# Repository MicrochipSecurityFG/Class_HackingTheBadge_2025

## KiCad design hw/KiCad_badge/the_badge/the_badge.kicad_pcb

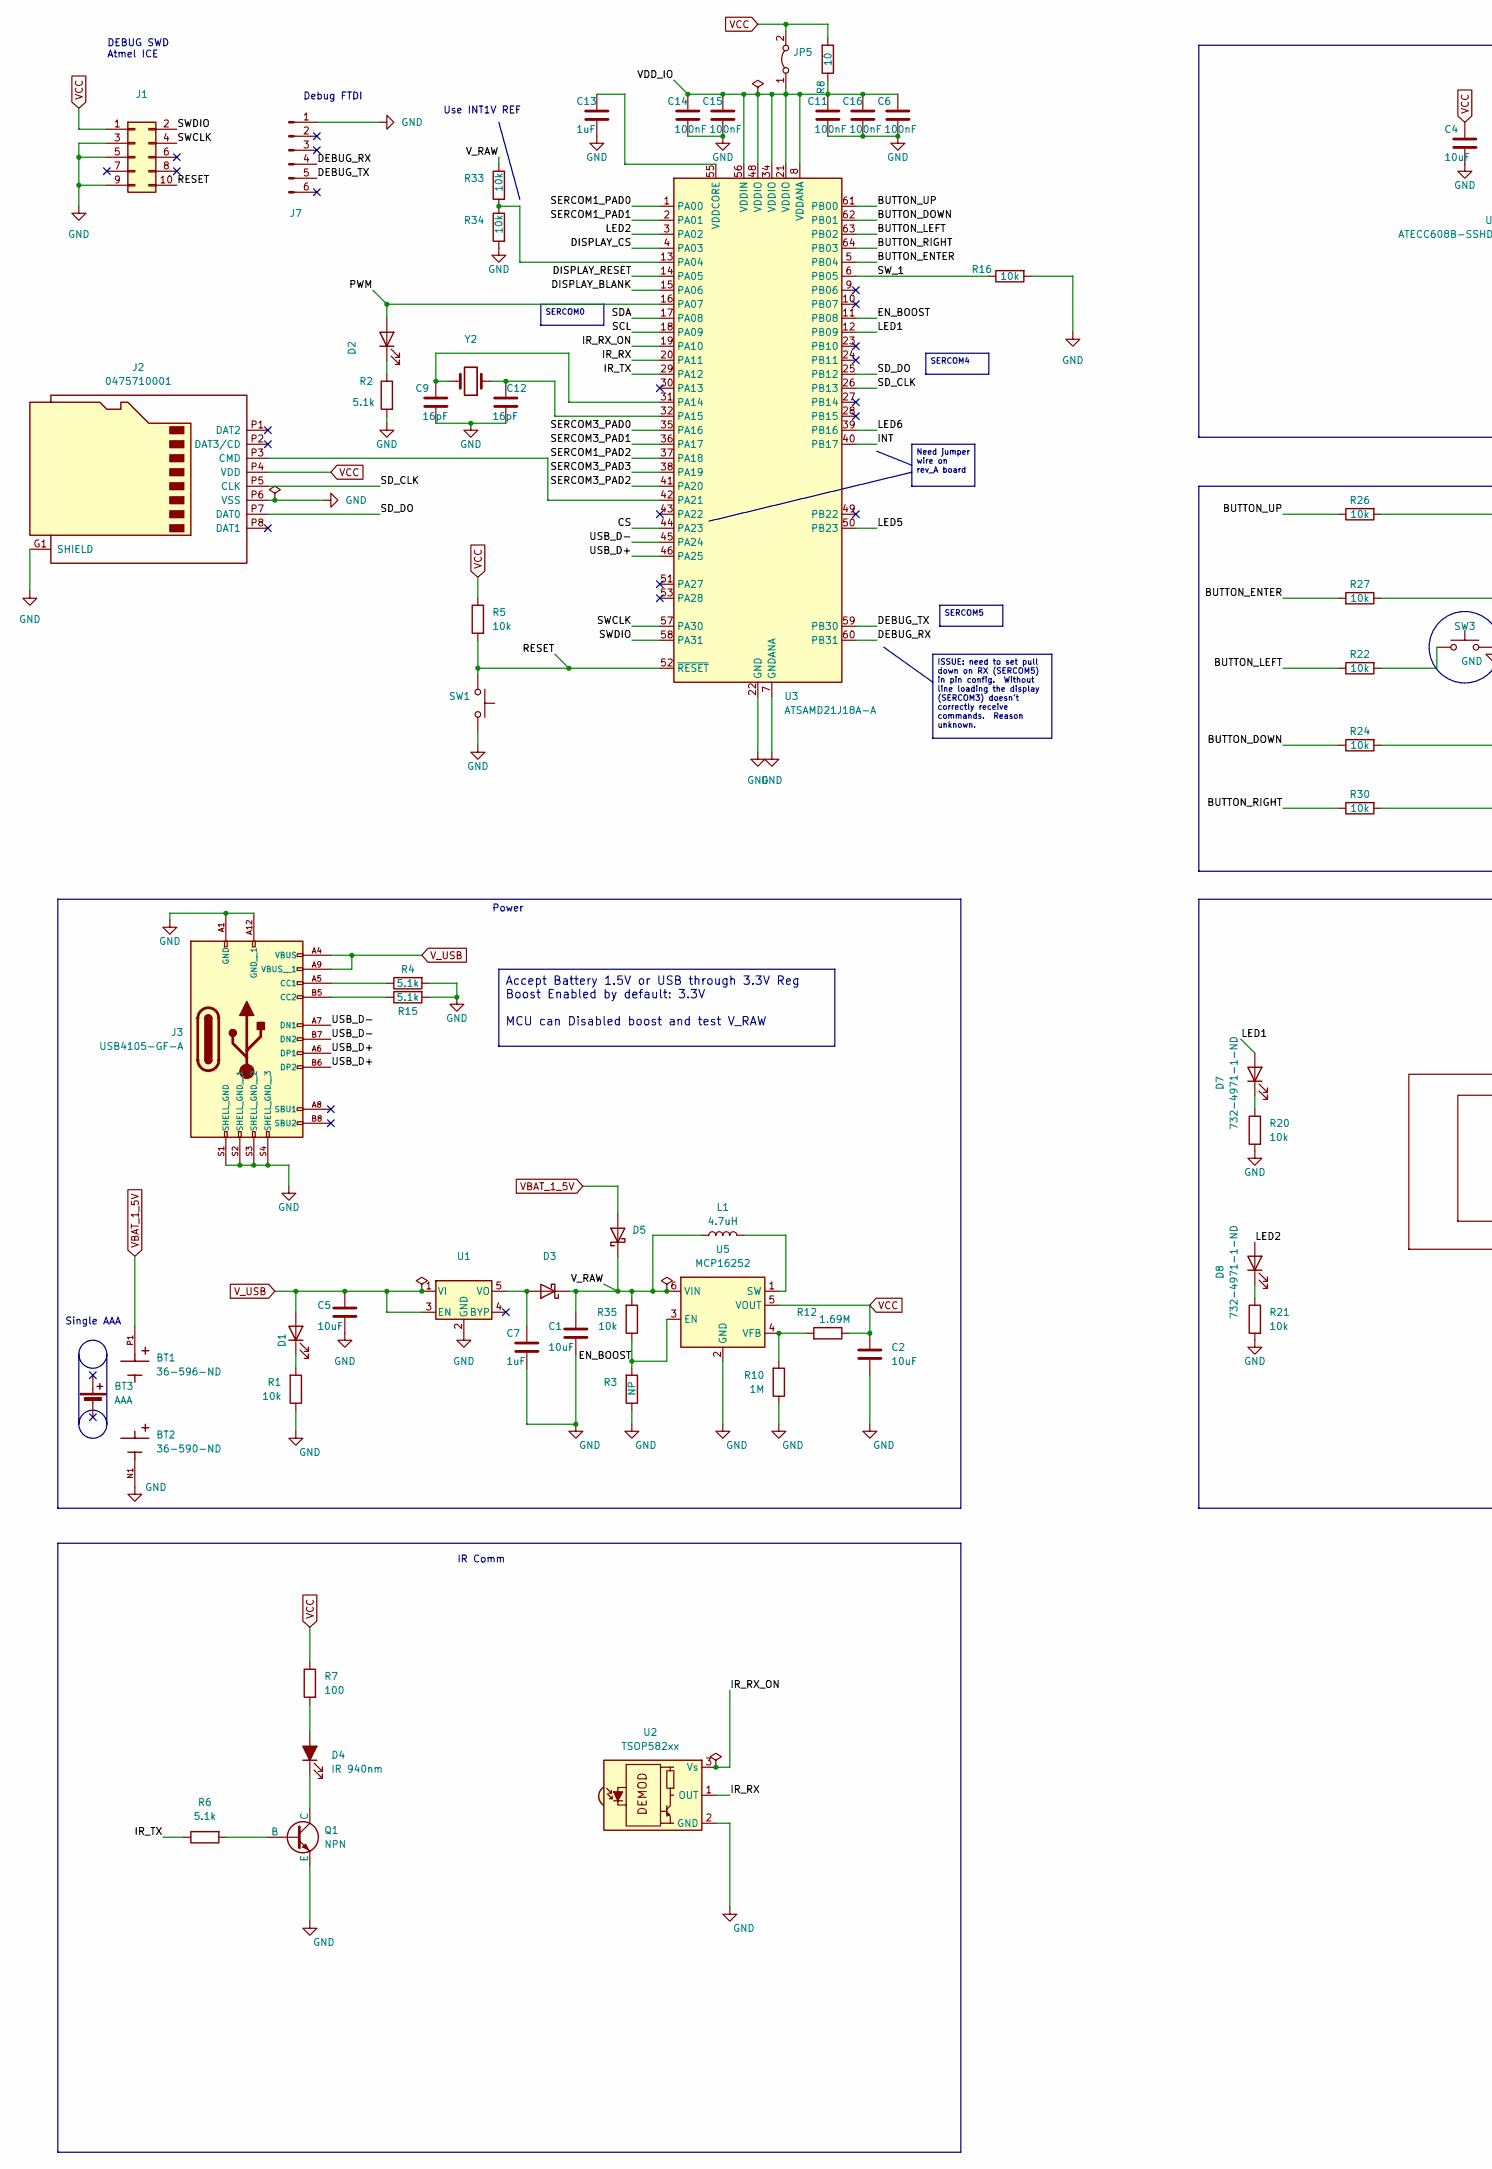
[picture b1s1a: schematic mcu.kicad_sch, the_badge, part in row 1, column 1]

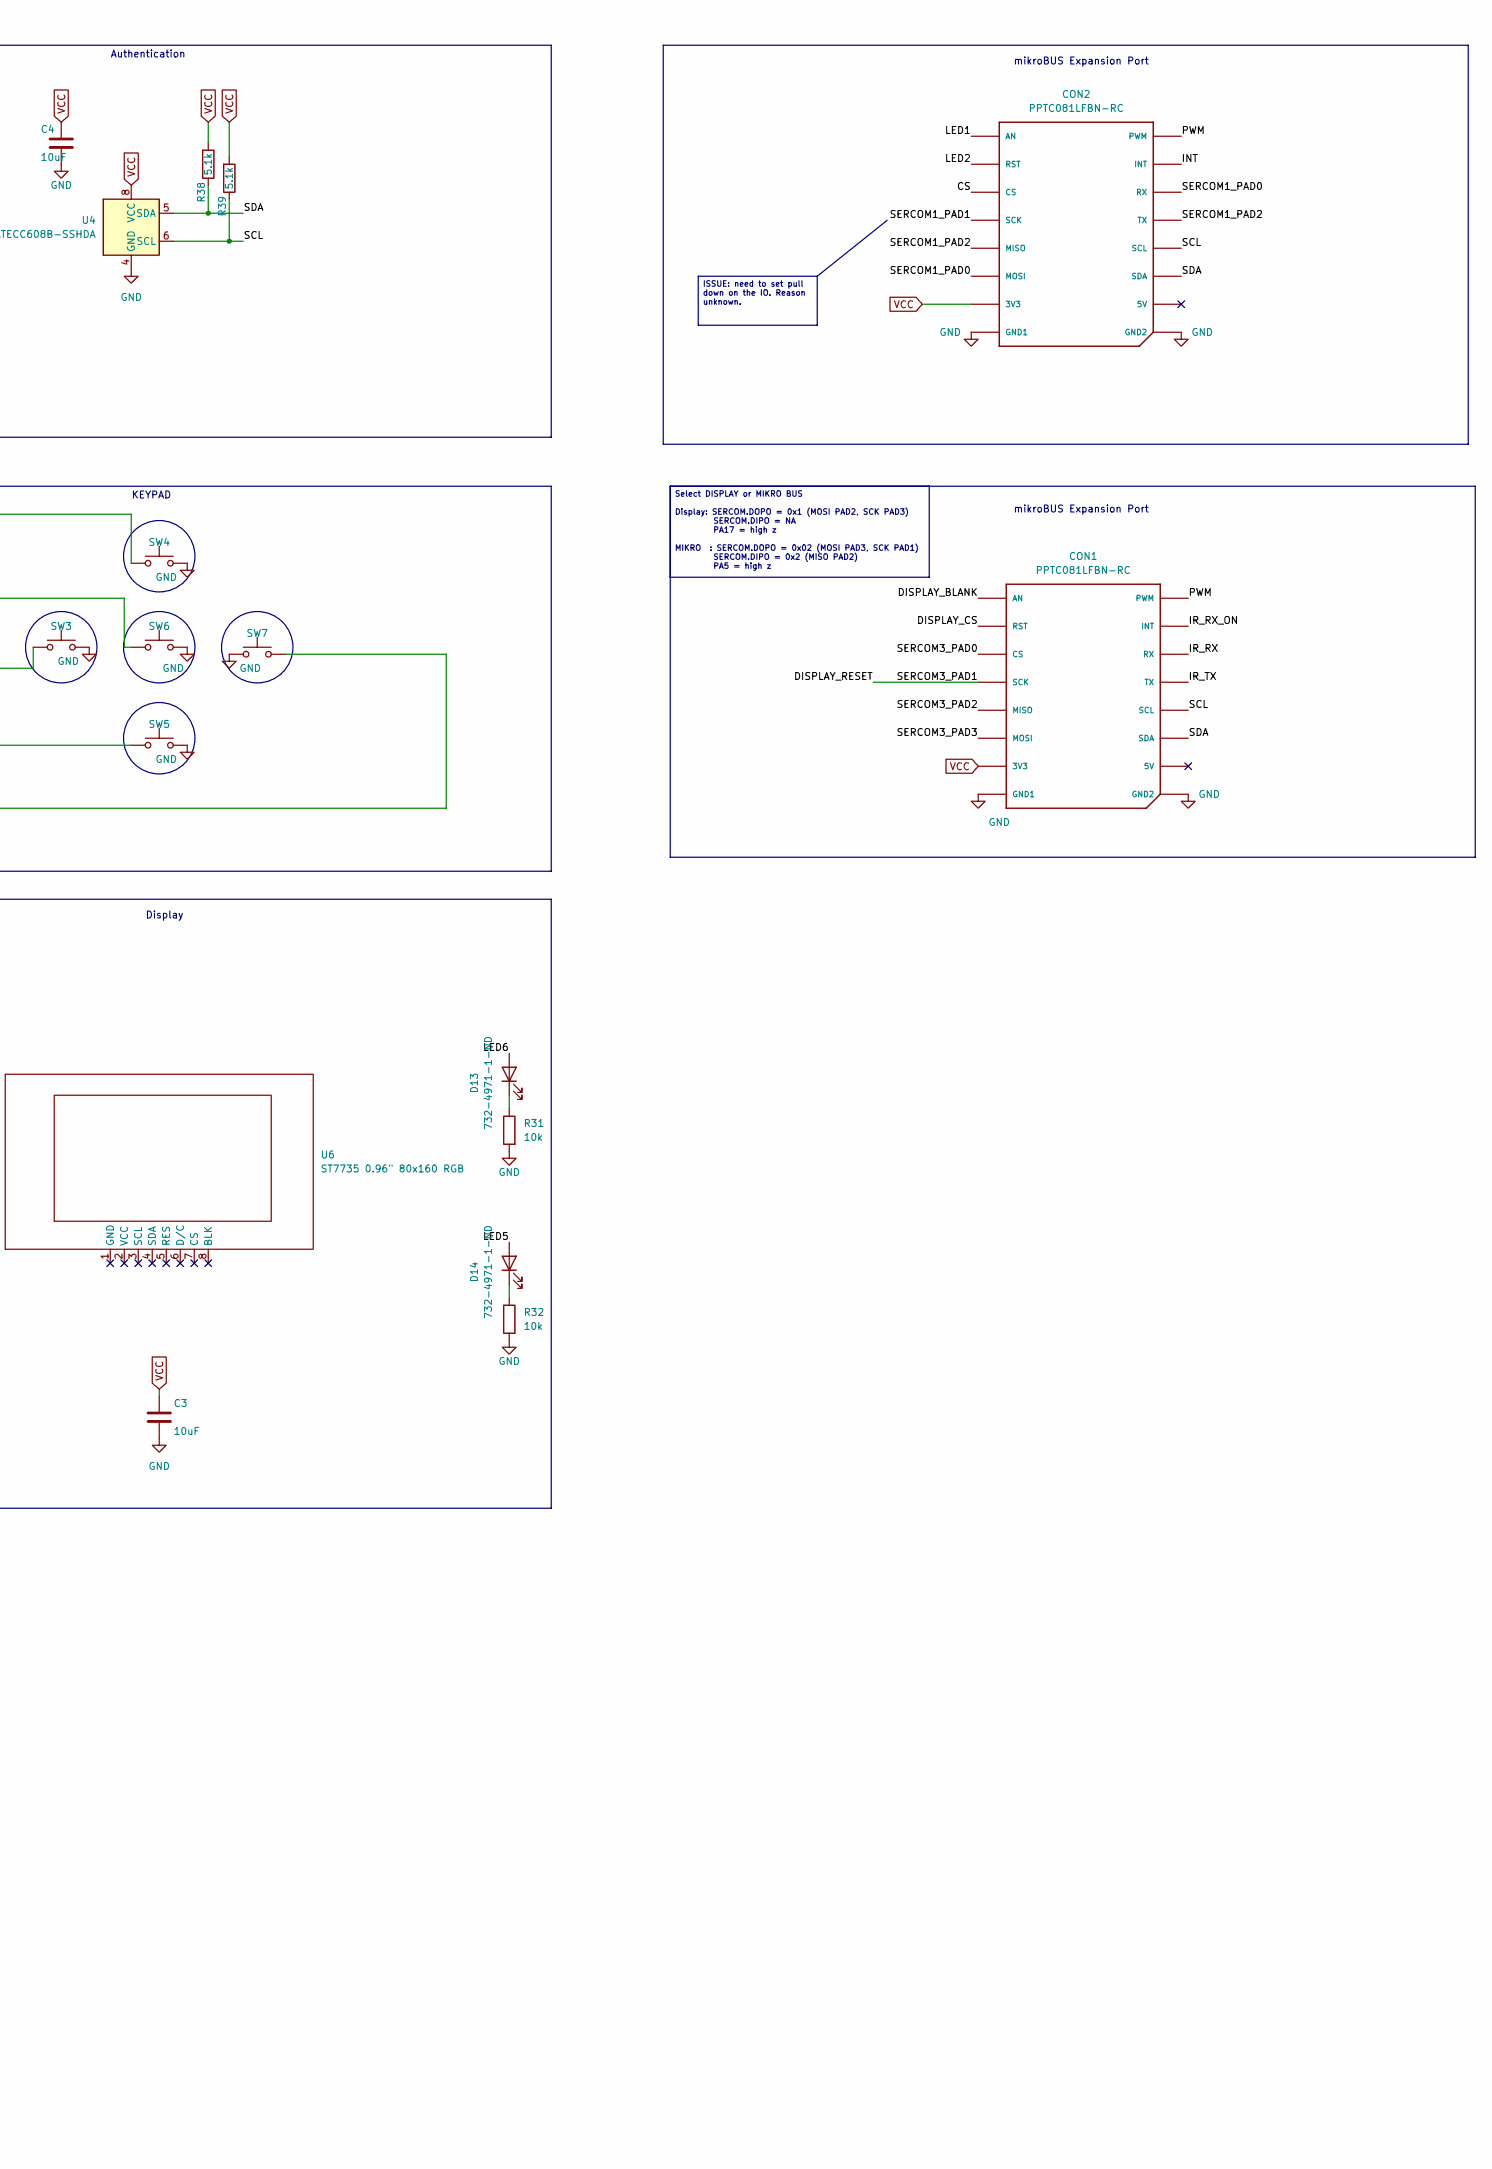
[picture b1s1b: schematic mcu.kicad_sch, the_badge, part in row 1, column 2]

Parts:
BT1: 36-596-ND; BAT_596; PARTREV D; Digikey 36-596-ND
BT2: 36-590-ND; BAT_590; PARTREV E; Digikey 36-590-ND
BT3: AAA; BatteryHolder_Keystone_2466_1xAAA
C1, C2, C3, C4, C5: 10uF; C_0603_1608Metric; Digikey 587-5869-1-ND
C6, C11, C14, C15, C16: 100nF; C_0603_1608Metric; Digikey 311-1088-1-ND
C7, C13: 1uF; C_0603_1608Metric; Digikey 311-1446-1-ND
C9, C12: 16pF; C_0603_1608Metric; Digikey 311-3964-1-ND
CON1, CON2: PPTC081LFBN-RC; MIKROBUS_HOST_CONN
D1, D2, D7, D8, D13, D14: 732-4971-1-ND; LED_0603_1608Metric; Digikey 732-4971-1-ND
D3, D5: D_Schottky; D_SOD-523; Digikey RB520S30T1GOSCT-ND
D4: IR 940nm; LED_0603_1608Metric; Digikey 3147-B13V1IR--20C000114U1930CT-ND
J1: 1156861; PinHeader_2x05_P1.27mm_Vertical_SMD; Digikey 277-1156861CT-ND
J2: 0475710001; 47571-0001_MOL; Digikey WM9731CT-ND
J3: USB4105-GF-A; USB_C_Receptacle_GCT_USB4105-xx-A_16P_TopMnt_Horizontal; PARTREV B3; Digikey 2073-USB4105-GF-ACT-ND
J7: Conn_01x06_Pin; PinHeader_1x06_P2.54mm_Vertical; Digikey 732-5319-ND
JP5: M50-3530242; PinHeader_1x02_P2.54mm_Vertical; Digikey SAM1112-02-ND (use cheaper part here), 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
L1: 4.7uH; L_0805_2012Metric; Digikey 445-8659-1-ND
Q1: NPN; SOT-23-3; Digikey MMBT3904-FDICT-ND
R1, R5, R16, R20, R21, R22, R24, R26, R27, R30, R31, R32, R33, R34, R35: 10k; R_0603_1608Metric; Digikey 311-10.0KHRCT-ND
R2, R4, R6, R15, R38, R39: 5.1k; R_0603_1608Metric; Digikey 311-5.10KHRCT-ND
R3: NP; R_0603_1608Metric; Digikey NA
R7: 100; R_0603_1608Metric; Digikey 311-100HRCT-ND
R8: 10; R_0603_1608Metric; Digikey 311-10.0HRCT-ND
R10: 1M; R_0603_1608Metric; Digikey 311-1.00MHRCT-ND
R12: 1.69M; R_0603_1608Metric; Digikey 13-RC0603FR-071M69LCT-ND
SW1, SW3, SW4, SW5, SW6, SW7: TS02-66-70-BK-160-LCR-D; SW_PUSH_6mm_H4.3mm; Digikey 2223-TS02-66-70-BK-160-LCR-D-ND
U1: MIC5301; TSOP-5_1.65x3.05mm_P0.95mm; Digikey 576-2840-1-ND
U2: TSOP582xx; Vishay_MINICAST-3Pin; Digikey TSOP58238-ND
U3: ATSAMD21J18A-A; TQFP-64_10x10mm_P0.5mm; Digikey ATSAMD21J18A-AUTCT-ND
U4: ATECC608B-SSHDA; SOIC-8_3.9x4.9mm_P1.27mm; Digikey 150-ATECC608B-SSHDA-TCT-ND
U5: MCP16252; SOT-23-6; Digikey MCP16252T-I/CHCT-ND
U6: ST7735 0.96" 80x160 RGB; Digikey NA
Y2: 049SS2-24.000F20DTLJK; Crystal_SMD_HC49-SD; Digikey XC1001CT-ND

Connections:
/mcu/BUTTON_DOWN: R24.1, U3.62 (PB01)
/mcu/BUTTON_ENTER: R27.2, U3.5 (PB04)
/mcu/BUTTON_LEFT: R22.1, U3.63 (PB02)
/mcu/BUTTON_RIGHT: R30.1, U3.64 (PB03)
/mcu/BUTTON_UP: R26.1, U3.61 (PB00)
/mcu/CS: CON2.P3 (CS), U3.44 (PA23)
/mcu/DEBUG_RX: J7.4, U3.60 (PB31)
/mcu/DEBUG_TX: J7.5, U3.59 (PB30)
/mcu/DISPLAY_BLANK: CON1.P1 (AN), U3.15 (PA06)
/mcu/DISPLAY_CS: CON1.P2 (RST), U3.4 (PA03)
/mcu/DISPLAY_RESET: CON1.P4 (SCK), U3.14 (PA05), U3.36 (PA17)
/mcu/EN_BOOST: R3.2, R35.1, U3.11 (PB08), U5.3 (EN)
/mcu/INT: CON2.P15 (INT), U3.40 (PB17)
/mcu/IR_RX: CON1.P14 (RX), U2.1 (OUT), U3.20 (PA11)
/mcu/IR_RX_ON: CON1.P15 (INT), U2.3 (Vs), U3.19 (PA10)
/mcu/IR_TX: CON1.P13 (TX), R6.1, U3.29 (PA12)
/mcu/LED1: CON2.P1 (AN), D7.2 (A), U3.12 (PB09)
/mcu/LED2: CON2.P2 (RST), D8.2 (A), U3.3 (PA02)
/mcu/LED5: D14.2 (A), U3.50 (PB23)
/mcu/LED6: D13.2 (A), U3.39 (PB16)
/mcu/PWM: CON1.P16 (PWM), CON2.P16 (PWM), D2.2 (A), U3.16 (PA07)
/mcu/RESET: J1.10, R5.2, SW1.2, U3.52 (~RESET)
/mcu/SCL: CON1.P12 (SCL), CON2.P12 (SCL), R39.1, U3.18 (PA09), U4.6 (SCL)
/mcu/SDA: CON1.P11 (SDA), CON2.P11 (SDA), R38.1, U3.17 (PA08), U4.5 (SDA)
/mcu/SD_CLK: J2.P5 (CLK), U3.26 (PB13)
/mcu/SD_DO: J2.P7 (DAT0), U3.25 (PB12)
/mcu/SERCOM1_PAD0: CON2.P6 (MOSI), CON2.P14 (RX), U3.1 (PA00)
/mcu/SERCOM1_PAD1: CON2.P4 (SCK), U3.2 (PA01)
/mcu/SERCOM1_PAD2: CON2.P5 (MISO), CON2.P13 (TX), U3.37 (PA18)
/mcu/SERCOM3_PAD0: CON1.P3 (CS), U3.35 (PA16)
/mcu/SERCOM3_PAD2: CON1.P5 (MISO), U3.41 (PA20)
/mcu/SERCOM3_PAD3: CON1.P6 (MOSI), U3.38 (PA19)
/mcu/SWCLK: J1.4, U3.57 (PA30)
/mcu/SWDIO: J1.2, U3.58 (PA31)
/mcu/SW_1: R16.1, U3.6 (PB05)
/mcu/USB_D+: J3.A6 (DP1), J3.B6 (DP2), U3.46 (PA25)
/mcu/USB_D-: J3.A7 (DN1), J3.B7 (DN2), U3.45 (PA24)
/mcu/VDD_IO: C6.1, C11.1, C14.1, C15.1, C16.1, JP5.1 (A), R8.1, U3.8 (VDDANA), U3.21 (VDDIO), U3.34 (VDDIO), U3.48 (VDDIO), U3.56 (VDDIN)
/mcu/V_RAW: C1.1, D3.1 (K), D5.1 (K), L1.1, R33.1, R35.2, U5.6 (VIN)
GND: BT2.N1, C1.2, C2.1, C3.2, C4.2, C5.1, C6.2, C7.2, C9.2, C11.2, C12.2, C13.2, C14.2, C15.2, C16.2, CON1.P8 (GND1), CON1.P9 (GND2), CON2.P8 (GND1), CON2.P9 (GND2), J1.3, J1.5, J1.9, J2.G1 (SHIELD), J2.G2 (SHIELD), J2.G3 (SHIELD), J2.G4 (SHIELD), J2.G5 (SHIELD), J2.P6 (VSS), J3.A1 (GND), J3.A12 (GND__1), J3.S1 (SHELL_GND), J3.S2 (SHELL_GND__1), J3.S3 (SHELL_GND__2), J3.S4 (SHELL_GND__3), J7.1, Q1.2 (E), R1.1, R2.2, R3.1, R4.2, R10.1, R15.2, R16.2, R20.2, R21.2, R31.2, R32.2, R34.2, SW1.1, SW3.2, SW4.2, SW5.2, SW6.2, SW7.2, U1.2 (GND), U2.2 (GND), U3.7 (GNDANA), U3.22 (GND), U3.33 (GND), U3.47 (GND), U3.54 (GND), U4.4 (GND), U5.2 (GND)
unnamed: D1.1 (K), R1.2
unnamed: D2.1 (K), R2.1
unnamed: C7.1, D3.2 (A), U1.5 (VO)
unnamed: D4.2 (A), R7.2
unnamed: D4.1 (K), Q1.3 (C)
unnamed: D7.1 (K), R20.1
unnamed: D8.1 (K), R21.1
unnamed: D13.1 (K), R31.1
unnamed: D14.1 (K), R32.1
unnamed: J2.P3 (CMD), U3.42 (PA21)
unnamed: J3.A5 (CC1), R4.1
unnamed: J3.B5 (CC2), R15.1
unnamed: Q1.1 (B), R6.2
unnamed: R22.2, SW3.1
unnamed: R24.2, SW5.1
unnamed: R26.2, SW4.1
unnamed: R27.1, SW6.1
unnamed: R30.2, SW7.1
unnamed: R33.2, R34.1, U3.13 (PA04)
unnamed: C9.1, U3.31 (PA14), Y2.2
unnamed: C12.1, U3.32 (PA15), Y2.1
unnamed: C13.1, U3.55 (VDDCORE)
unnamed: L1.2, U5.1 (SW)
unnamed: R10.2, R12.2, U5.4 (VFB)
VBAT_1_5V: BT1.P1, D5.2 (A)
VCC: C2.2, C3.1, C4.1, CON1.P7 (3V3), CON2.P7 (3V3), J1.1, J2.P4 (VDD), JP5.2 (B), R5.1, R7.1, R8.2, R12.1, R38.2, R39.2, U4.8 (VCC), U5.5 (VOUT)
V_USB: C5.2, D1.2 (A), J3.A4 (VBUS), J3.A9 (VBUS__1), U1.1 (VI), U1.3 (EN)

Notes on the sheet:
KEYPAD
Use INT1V REF
mikroBUS Expansion Port
Authentication
Display
IR Comm
DEBUG SWD Atmel ICE
Debug FTDI
Single AAA
Power
ISSUE: need to set pull down on RX (SERCOM5) in pin config. Without line loading the display (SERCOM3) doesn't correctly receive commands. Reason unknown.
Accept Battery 1.5V or USB through 3.3V Reg Boost Enabled by default: 3.3V MCU can Disabled boost and test V_RAW
SERCOM0
SERCOM5
SERCOM4
Need jumper wire on rev_A board
Select DISPLAY or MIKRO BUS Display: SERCOM.DOPO = 0x1 (MOSI PAD2, SCK PAD3) SERCOM.DIPO = NA PA17 = high z MIKRO : SERCOM.DOPO = 0x02 (MOSI PAD3, SCK PAD1) SERCOM.DIPO = 0x2 (MISO PAD2) PA5 = high z
ISSUE: need to set pull down on the IO. Reason unknown.

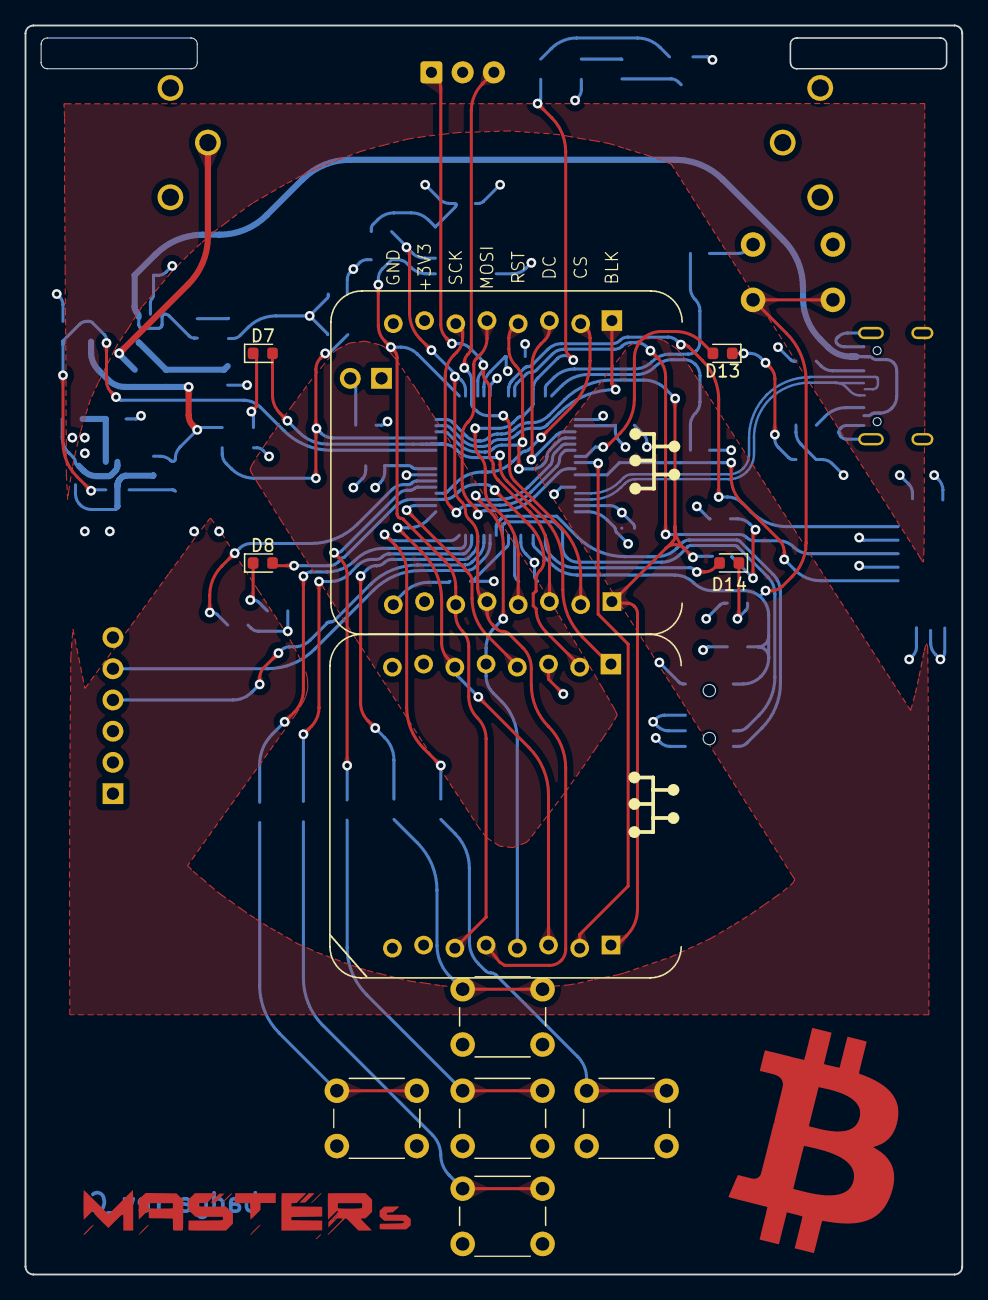
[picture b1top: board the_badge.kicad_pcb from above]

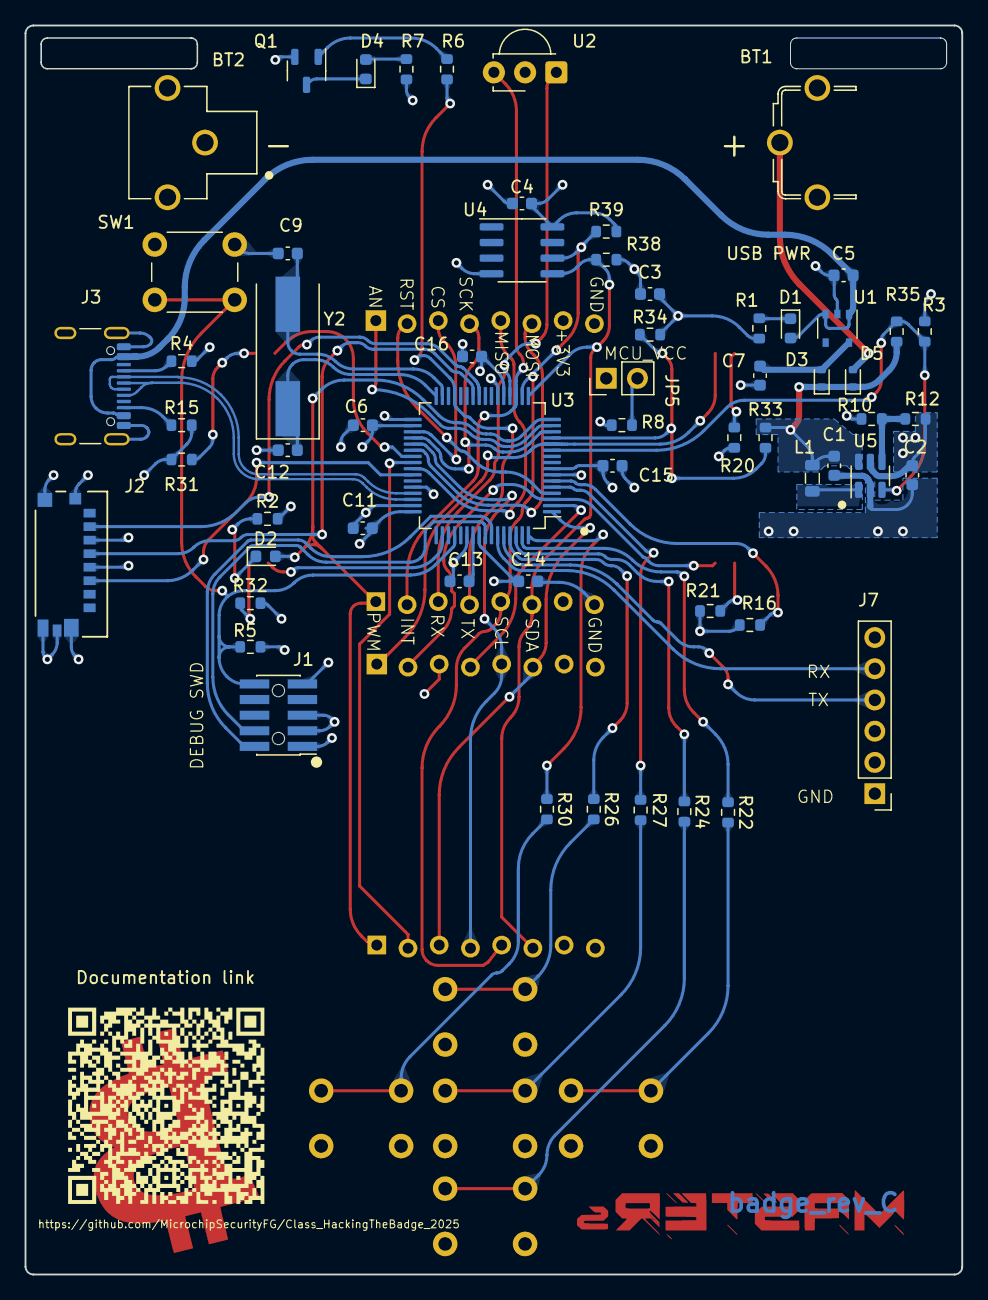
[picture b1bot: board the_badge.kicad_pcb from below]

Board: 4 copper layers, 76.2 x 101.6 mm, 72 parts (61 on the bottom side), 67 nets.

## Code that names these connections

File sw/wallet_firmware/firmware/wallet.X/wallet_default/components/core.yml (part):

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      - children:
        - attributes:
            id: core
            value: PA10
          type: Dynamic
        type: Values
      type: String
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      - children:
        - attributes:
            id: core
            value: PA11
          type: Dynamic
        type: Values
      type: String
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      - children:
        - attributes:
            id: core
            value: PA12
          type: Dynamic
        type: Values
      type: String
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      - children:
        - attributes:
            id: core
            value: PA16
          type: Dynamic
        type: Values
      type: String
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      - children:
        - attributes:
            id: core
            value: PA17
          type: Dynamic
        type: Values
      type: String
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      - children:
        - attributes:
            id: core
            value: PA18
          type: Dynamic
        type: Values
      type: String
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      - children:
        - attributes:
            id: core
            value: PA19
          type: Dynamic
        type: Values
      type: String
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      - children:
        - attributes:
            id: core
            value: PA02
          type: Dynamic
        type: Values
      type: String
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      - children:
        - attributes:
            id: core
            value: PA20
          type: Dynamic
        type: Values
      type: String
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      - children:
        - attributes:
            id: core
            value: PA21
          type: Dynamic
        type: Values
      type: String
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      - children:
        - attributes:
            id: core
            value: PA23
          type: Dynamic
        type: Values
      type: String
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      - children:
        - attributes:
            id: core
            value: PA03
          type: Dynamic
        type: Values
      type: String
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      - children:
        - attributes:
            id: core
            value: PA30
          type: Dynamic
        type: Values
      type: String
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      - children:
        - attributes:
            id: core
            value: PA31
          type: Dynamic
        type: Values
      type: String
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      - children:
        - attributes:
            id: core
            value: PA05
          type: Dynamic
        type: Values
      type: String
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      - children:
        - attributes:
            id: core
            value: PA07
          type: Dynamic
        type: Values
      type: String
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      - children:
        - attributes:
            id: core
            value: PA08
          type: Dynamic
        type: Values
      type: String
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      - children:
        - attributes:
            id: core
            value: PA09
          type: Dynamic
        type: Values
      type: String
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      - children:
        - attributes:
            id: core
            value: PB00
          type: Dynamic
        type: Values
      type: String
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      - children:
        - attributes:
            id: core
            value: PB01
          type: Dynamic
        type: Values
      type: String
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      - children:
        - attributes:
            id: core
            value: PB13
          type: Dynamic
        type: Values
      type: String
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      - children:
        - attributes:
            id: core
            value: PB16
          type: Dynamic
        type: Values
      type: String
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      - children:
        - attributes:
            id: core
            value: PB17
          type: Dynamic
        type: Values
      type: String
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      - children:
        - attributes:
            id: core
            value: PB02
          type: Dynamic
        type: Values
      type: String
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      - children:
        - attributes:
            id: core
            value: PB23
          type: Dynamic
        type: Values
      type: String
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      - children:
        - attributes:
            id: core
            value: PB03
          type: Dynamic
        type: Values
      type: String
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      - children:
        - attributes:
            id: core
            value: PB30
          type: Dynamic
        type: Values
      type: String
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      - children:
        - attributes:
            id: core
            value: PB31
          type: Dynamic
        type: Values
      type: String
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      - children:
        - attributes:
            id: core
            value: PB04
          type: Dynamic
        type: Values
      type: String
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      - children:
        - attributes:
            id: core
            value: PB09
          type: Dynamic
        type: Values
      type: String
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
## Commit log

2025-06-12 project init
2025-06-12 fixes
2025-06-13 clean up
2025-06-13 remove mistaken git ignore
2025-06-13 parameterized download tag name
2025-06-13 updated search space
2025-06-16 bug fixes
2025-06-30 add encryption attack and update to new mcc harmony
2025-06-30 new ep update
2025-06-30 setup for ep tag (one warning cleanup in ir.c)
2025-07-09 adjusted to make glitch demo
2025-07-28 build error fix
2025-07-28 clean ups
2025-07-29 always overwrite
2025-07-29 clean up maybe final
2025-09-03 adjustments to improve lcd menu and allow use without a PC
2025-09-04 add manuals, add bitcion serial port monitor to convert any recevied addr to a qr.
2025-09-04 updated gitignore
2025-09-04 updated build
2025-09-04 updated ignore
2025-09-04 added test entry
2025-09-04 added duplicate address entry in scratch_pad.txt for testing
2025-09-05 convert to 4 digit PIN
2025-09-08 test
2025-09-08 add multi address scrolling and copy from address queue
